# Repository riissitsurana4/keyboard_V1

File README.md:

# Keyboard_V1
Hello everyone!

This hardware project is a custom keyboard and  macro pad made using switches, a rotatory encoder, etc.

## PCB Design
### Keyboard 
The PCB was designed in **KiCad** and includes the following features:

* Cherry Mx Switches arranged in a matrix 
* Mini leds for underglow
* 2 rotary encoder
* NRF52840 as the MCU
* 1N4148 (diodes)
* 74HC14N and MT3608 to step up current for leds
* 74HC595 - Shift registers

The LEDs are placed under each key for per key under glow.
Using shift registers for columns.

https://kicanvas.org/?repo=https%3A%2F%2Fgithub.com%2Friissitsurana4%2Fkeyboard_V1%2Ftree%2Fmain%2FPCB%2FKeyboard

### Macro Pad
The PCB was designed in **KiCad** and includes the following features:
* Cherry Mx Switches arranged in a matrix 
* 2 rotary encoder
* NRF52840 as the MCU
* 
https://kicanvas.org/?repo=https%3A%2F%2Fgithub.com%2Friissitsurana4%2Fkeyboard_V1%2Ftree%2Fmain%2FPCB%2FMacropad

Using the NRF in both of them as it can be used wirelessly together

Both of the pcbs have a battery connector.

## Firmware
The firmware for this project is written in ZMK.
MAjor part of the firmware is AI written, mainly the keyboard part as i could not get the shift resistors part to work by myself.
It is located in a different repo 
https://github.com/riissitsurana4/keyboard_zmk
You can find the latest build at https://github.com/riissitsurana4/keyboard_zmk/actions/runs/29620562583

## Instructions
If you want to create this keyboard for yourself, you can find the pcb and the case designs in this repo. The case is designed to be 3d printed. 
Please refer to the above firmware section to download the latest version. You will need to flash both the mcu's with the latest build. 

NOTE: For the macropad PCB you would need to order a perforated side pcb so that the copper pads will flow over to the sides and make the pogo pin connection better. 

## BOM
| Item                  | Part Number      | Quantity | Link |
|-----------------------|------------------|----------|------|
| Microcontroller       | nRF52840         | 2        | https://robu.in/product/promicro-nrf52840-development-board/ |
| Diode                 | 1N4148           |       | https://stackskb.com/store/1n4148-through-hole-diode/ |
| Shift Register        | 74HC595          | 2        | https://robu.in/product/1-month-warranty-1354/ |
| Hex Schmitt Trigger   | 74HC14N          | 1        | https://robu.in/product/sn74hct14n-texas-instruments-logic-ic-inverter-hex-1-inputs-14-pins-dip-74hct14/ |
| DC-DC Boost Converter | MT3608           | 1        | https://robu.in/product/mt3608-xian-aerosemi-tech-boost-type-adjustable-2a-2v24v-sot-23-6-dc-dc-converters-rohs/ |
| Mini LEDs             | SK6812 MINI      |~90    |  |
| LiPo Battery          | 2000 mAh         | 1        |  |
| LiPo Battery          | 300 mAh          | 1        |  |
| Battery Connector     | JST-PH 2.0 (2-pin) | 2     |  |
| Switches              | Cherry-MX switches | ~100    |https://stackskb.com/store/akko-v3-cream-black-pro-switch-pack-of-45/  |

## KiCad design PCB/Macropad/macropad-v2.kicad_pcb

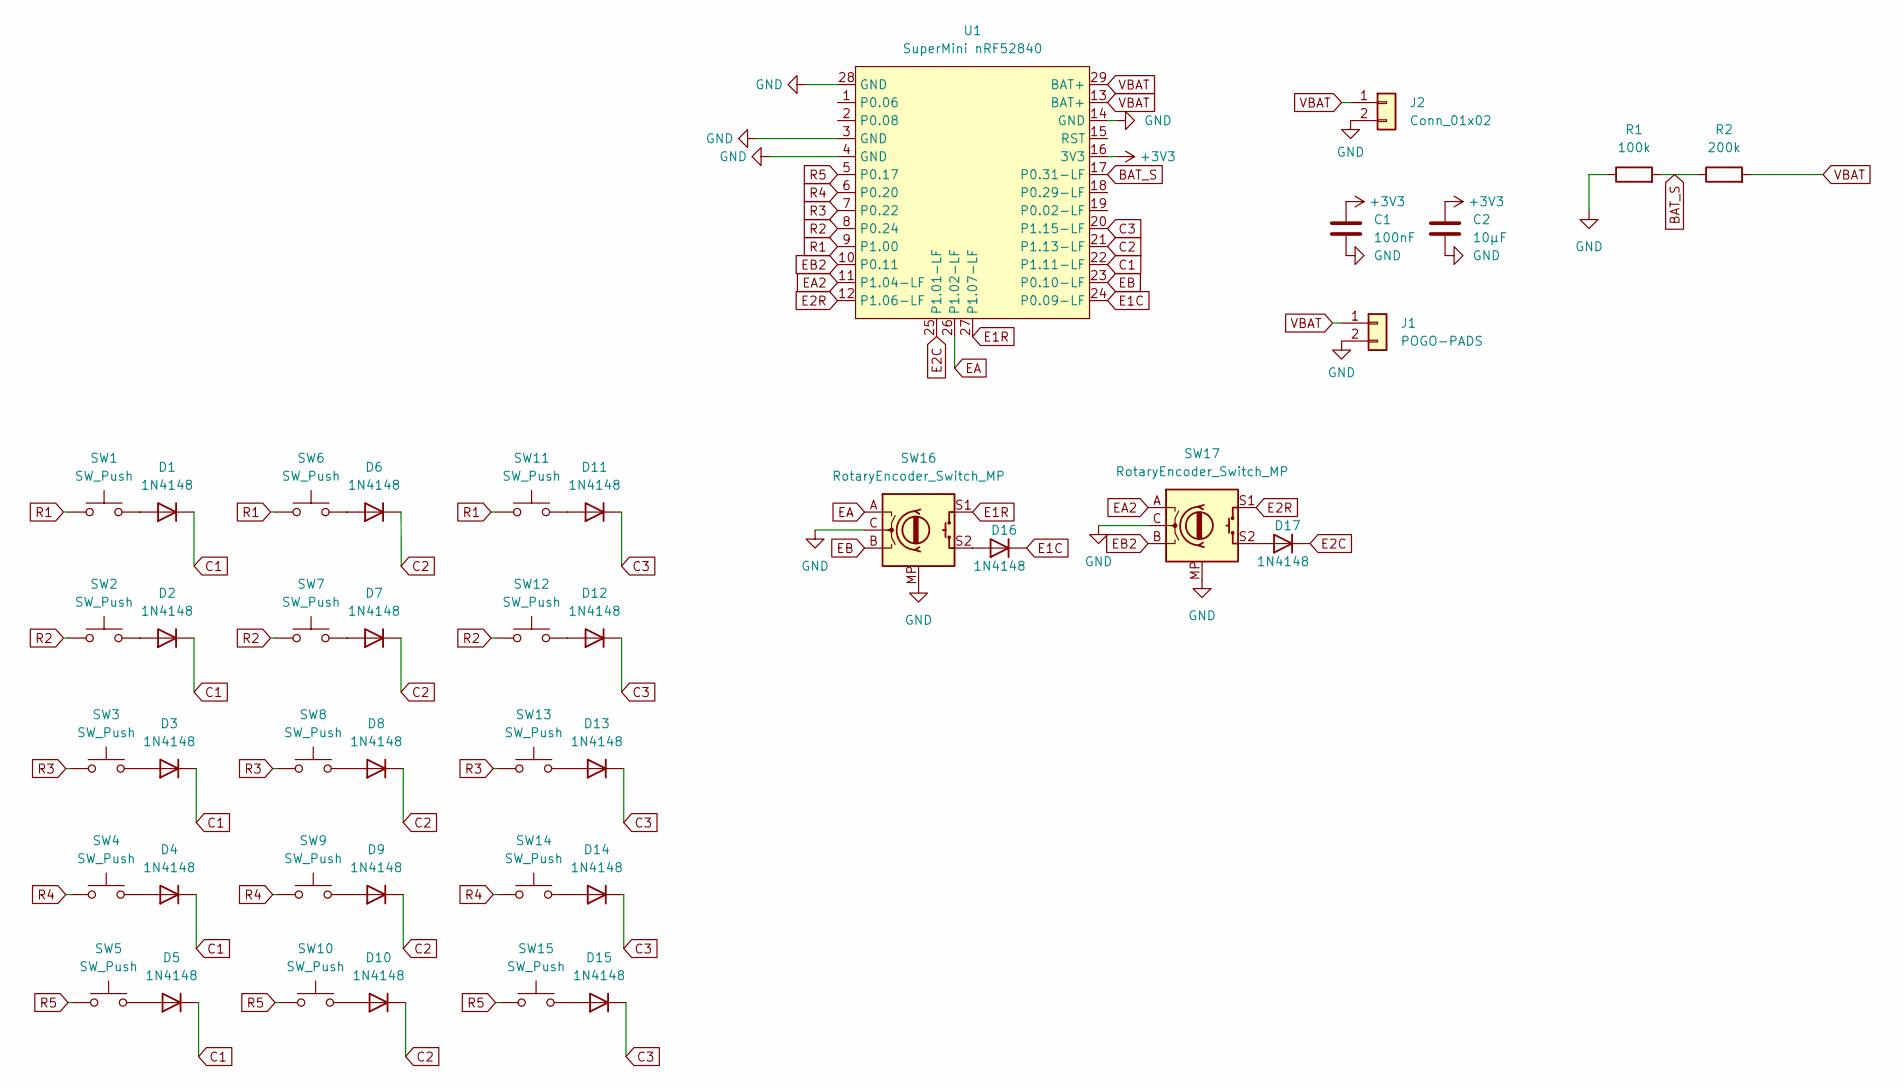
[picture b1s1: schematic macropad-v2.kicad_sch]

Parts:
C1: 100nF; C_Disc_D5.0mm_W2.5mm_P2.50mm
C2: 10µF; C_Disc_D5.0mm_W2.5mm_P2.50mm
D1, D2, D3, D4, D5, D6, D7, D8, D9, D10, D11, D12, D13, D14, D15, D16, D17: 1N4148; D_DO-35_SOD27_P7.62mm_Horizontal
J1: POGO-PADS; JST_PH_B2B-PH-K_1x02_P2.00mm_Vertical
J2: Conn_01x02; JST_PH_B2B-PH-K_1x02_P2.00mm_Vertical
R1: 100k; R_Axial_DIN0207_L6.3mm_D2.5mm_P7.62mm_Horizontal
R2: 200k; R_Axial_DIN0207_L6.3mm_D2.5mm_P7.62mm_Horizontal
SW1, SW2, SW3, SW4, SW5, SW6, SW7, SW8, SW9, SW10, SW11, SW12, SW13, SW14, SW15: SW_Push; SW_Cherry_MX_1.00u_PCB
SW16, SW17: RotaryEncoder_Switch_MP; RotaryEncoder_Alps_EC11E-Switch_Vertical_H20mm
U1: SuperMini nRF52840; nice_nano_AH_USBup

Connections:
+3V3: C1.1, C2.1, U1.16 (3V3)
BAT_S: R1.2, R2.1, U1.17 (P0.31-LF)
C1: D1.1 (K), D2.1 (K), D3.1 (K), D4.1 (K), D5.1 (K), U1.22 (P1.11-LF)
C2: D6.1 (K), D7.1 (K), D8.1 (K), D9.1 (K), D10.1 (K), U1.21 (P1.13-LF)
C3: D11.1 (K), D12.1 (K), D13.1 (K), D14.1 (K), D15.1 (K), U1.20 (P1.15-LF)
E1C: D16.1 (K), U1.24 (P0.09-LF)
E1R: SW16.S1, U1.27 (P1.07-LF)
E2C: D17.1 (K), U1.25 (P1.01-LF)
E2R: SW17.S1, U1.12 (P1.06-LF)
EA: SW16.A, U1.26 (P1.02-LF)
EA2: SW17.A, U1.11 (P1.04-LF)
EB: SW16.B, U1.23 (P0.10-LF)
EB2: SW17.B, U1.10 (P0.11)
GND: C1.2, C2.2, J1.2, J2.2, R1.1, SW16.C, SW16.MP, SW17.C, SW17.MP, U1.3 (GND), U1.4 (GND), U1.14 (GND), U1.28 (GND)
unnamed: D1.2 (A), SW1.2
unnamed: D2.2 (A), SW2.2
unnamed: D3.2 (A), SW3.2
unnamed: D4.2 (A), SW4.2
unnamed: D5.2 (A), SW5.2
unnamed: D6.2 (A), SW6.2
unnamed: D7.2 (A), SW7.2
unnamed: D8.2 (A), SW8.2
unnamed: D9.2 (A), SW9.2
unnamed: D10.2 (A), SW10.2
unnamed: D11.2 (A), SW11.2
unnamed: D12.2 (A), SW12.2
unnamed: D13.2 (A), SW13.2
unnamed: D14.2 (A), SW14.2
unnamed: D15.2 (A), SW15.2
unnamed: D16.2 (A), SW16.S2
unnamed: D17.2 (A), SW17.S2
R1: SW1.1, SW6.1, SW11.1, U1.9 (P1.00)
R2: SW2.1, SW7.1, SW12.1, U1.8 (P0.24)
R3: SW3.1, SW8.1, SW13.1, U1.7 (P0.22)
R4: SW4.1, SW9.1, SW14.1, U1.6 (P0.20)
R5: SW5.1, SW10.1, SW15.1, U1.5 (P0.17)
VBAT: J1.1, J2.1, R2.2, U1.13 (BAT+), U1.29 (BAT+)

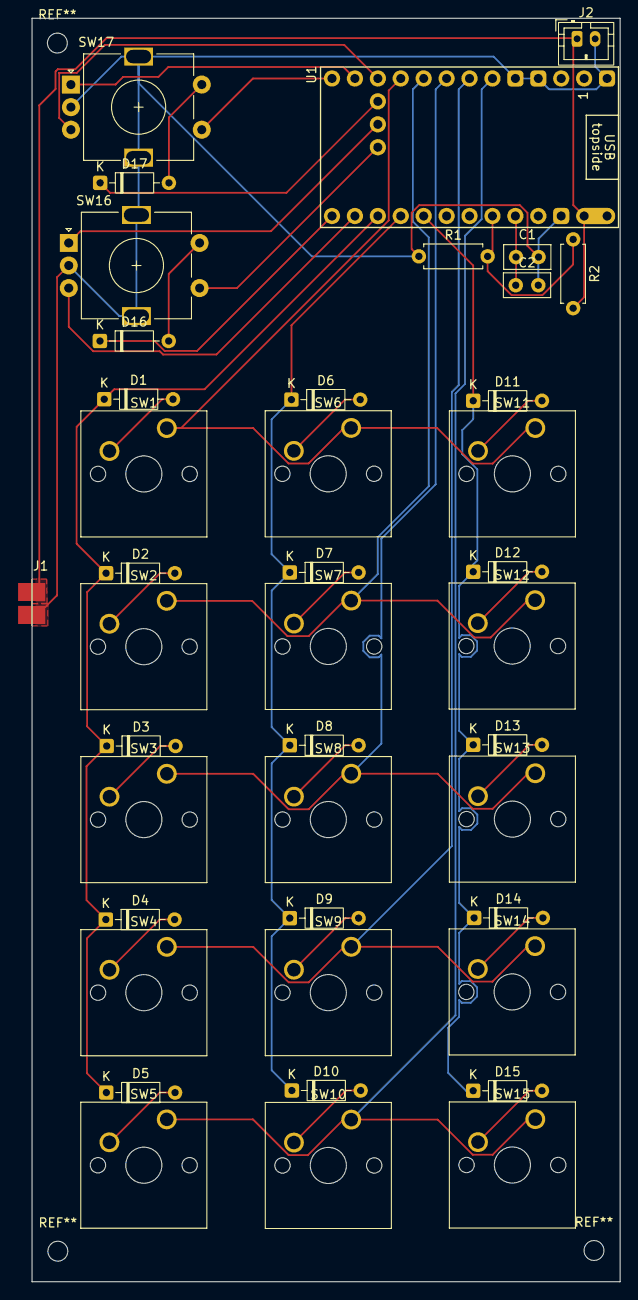
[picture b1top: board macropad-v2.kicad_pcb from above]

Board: 2 copper layers, 65.2 x 140.0 mm, 41 parts (0 on the bottom side), 37 nets.
